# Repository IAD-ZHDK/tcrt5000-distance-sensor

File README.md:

# tcrt5000 distane senor
 Grove compatible breakout for the tcrt5000 with window comparator (to select the active max and min range of the sensor). Range from <1cm to  8cm. Open Hardware

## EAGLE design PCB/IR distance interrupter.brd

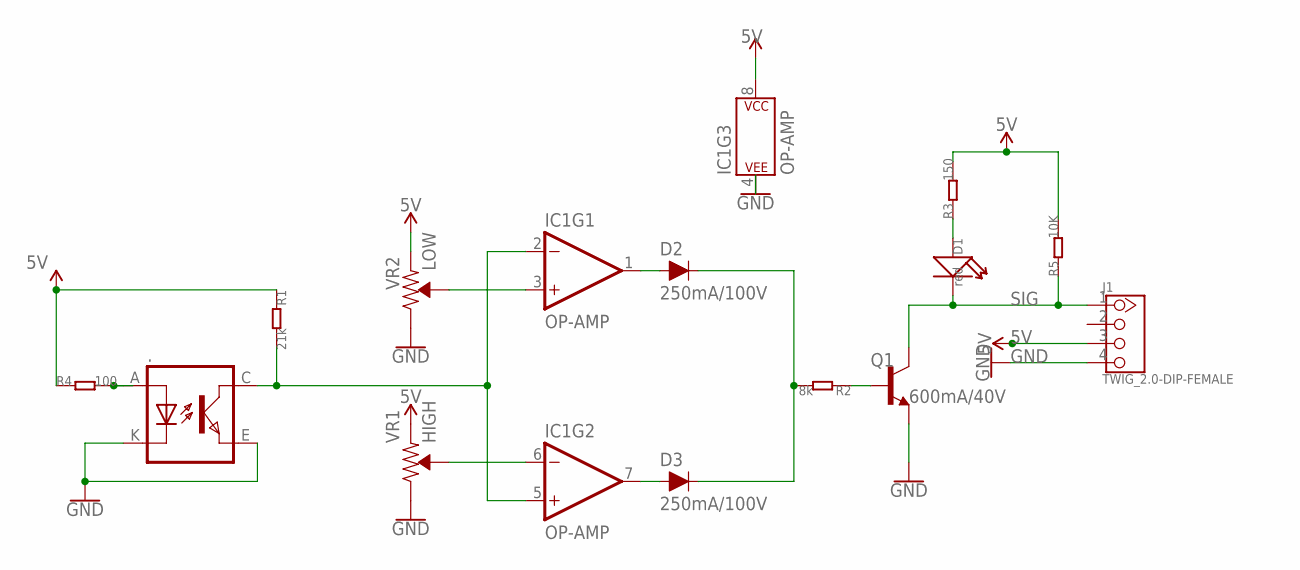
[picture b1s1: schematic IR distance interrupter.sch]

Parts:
.: TCRT5000
D1: red; LED0603
D2, D3: 250mA/100V; SOD-323
IC1: OP-AMP; SO08
J1: TWIG_2.0-DIP-FEMALE; 2.0_1X4
Q1: 600mA/40V; SOT23-3
R1: 21k; 0603_S
R2: 8k; 0603_S
R3: 150; 0603_S
R4: 100; 0603_S
R5: 10K; 0603_S
VR1: HIGH; TRIMPOT-SMD-5MM
VR2: LOW; TRIMPOT-SMD-5MM

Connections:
5V: IC1.8 (P$V+), J1.3, R1.1, R3.2, R4.1, R5.2, VR1.A (CCW), VR2.A (CCW)
GND: ..E (EMITTER), ..K (CATHODE), IC1.4 (P$V-), J1.4, Q1.2 (E), VR1.C (CW), VR2.C (CW)
unnamed: IC1.6 (-IN), VR1.B (WIPER)
unnamed: D1.1 (+), R3.1
unnamed: ..A (ANODE), R4.2
unnamed: IC1.3 (+IN), VR2.B (WIPER)
unnamed: D2.A, IC1.1 (OUT)
unnamed: D3.A, IC1.7 (OUT)
unnamed: Q1.1 (B), R2.1
unnamed: D2.C, D3.C, R2.2
unnamed: ..C (COLLECTOR), IC1.2 (-IN), IC1.5 (+IN), R1.2
SIG: D1.2 (-), J1.1, Q1.3 (C), R5.1

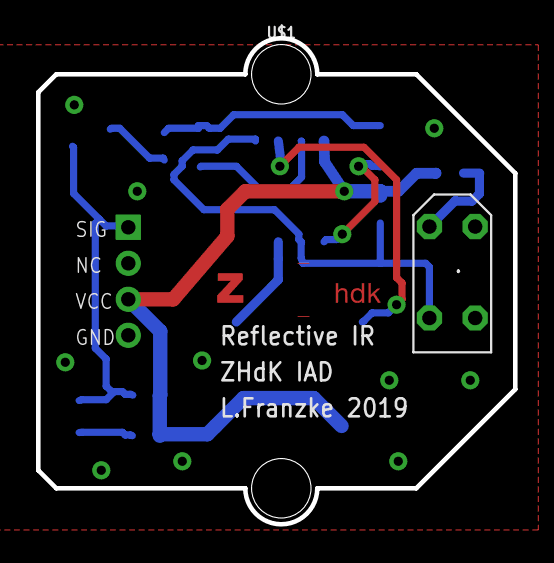
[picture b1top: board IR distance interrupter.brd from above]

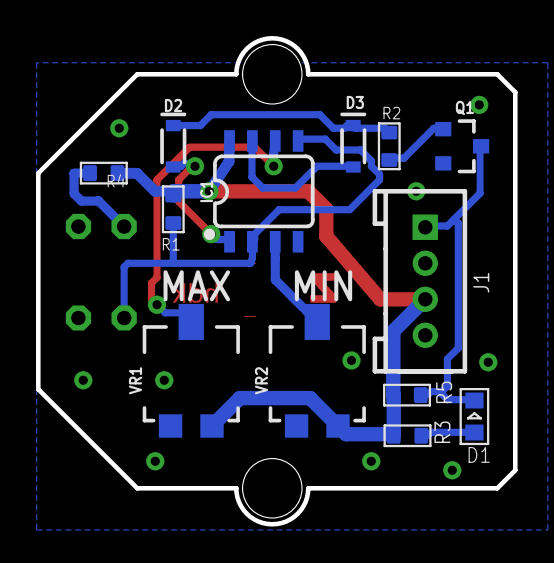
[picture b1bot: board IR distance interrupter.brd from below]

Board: 2 copper layers, 26.5 x 27.0 mm, 17 parts (13 on the bottom side), 12 nets.

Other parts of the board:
U$1, U$3: STAND-OFF
U$2: ZHDK_LOGO

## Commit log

2019-08-14 Initial upload
2019-08-14 Image in readme

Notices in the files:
parts and their libraries:
SparkFun-Resistors: Licensing: Creative Commons ShareAlike 4.0 International - https://creativecommons.org/licenses/by-sa/4.0
